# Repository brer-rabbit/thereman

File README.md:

# Annoying Thereman - light sensitive buzzing companion

This repo contains the design and build info for Thereman, a light sensitive buzzing companion.  Very useful for a variety of buzzing sounds.

The Thereman contains two LDRs (Light Dependent Resistors) and a dual 555 timer pretty much like an Atari Punk Console.  The LDRs control pitch and pulse width.

# Build

The kit contains a PCB with the dual 555 timer (a 556), the LDRs, eye LEDs, and some passive components on the front, pre-soldered (lead free).  The back requires soldering a couple components.  I'm assuming you're using regular solder wire (if you're using liquid solder I assume you know what you're doing).

## Prep

Tin the pads first.  Shown below, tin the pads marked in green.  The pads in red should not be tinned.

Optionally: if you'd like a loop of wire to hang the Thereman from, tin the yellow pads.  These are not electrically connected.  You can solder a wire to one or between them to create a loop.

Just a touch of solder for tinning please.  And you don't want solder poking up.  Keep it flat and level so components lay flat.

## Switch

The switch has a few small pads; it's easiest to do this first before the other components clutter the space.  The on/off switch sticks out the side of the Thereman.

Once done congrats!  You've soldered the smallest component of the project.  Everything else ought to be easy.

## Piezo Buzzer

The piezo buzzer is the black square that is responsible for the great sound of the Thereman.  It goes in the very middle; it's not polarized and can be installed in either direction.

## Battery Retainers

Install the top battery retainer.  Two of the three pads keep the battery retainer in place and make an electrical connection.  The middle pad is not soldered.  Of the two pads to solder, the pad that is at the top may be easiest to do first.  Then the pad right next to the piezo.

The bottom two battery retainers need to be oriented so one can insert batteries.

Also, keep the battery retainers slightly apart so they do not touch.

## Cleaning

A bit of isopropyl alcohol can be used for cleaning.  Try not to get alcohol in the switch or the piezo buzzer.

## Flip the switch!

With batteries installed (positive side facing up in retainer) flip the switch.  Your Thereman should now start annoying!

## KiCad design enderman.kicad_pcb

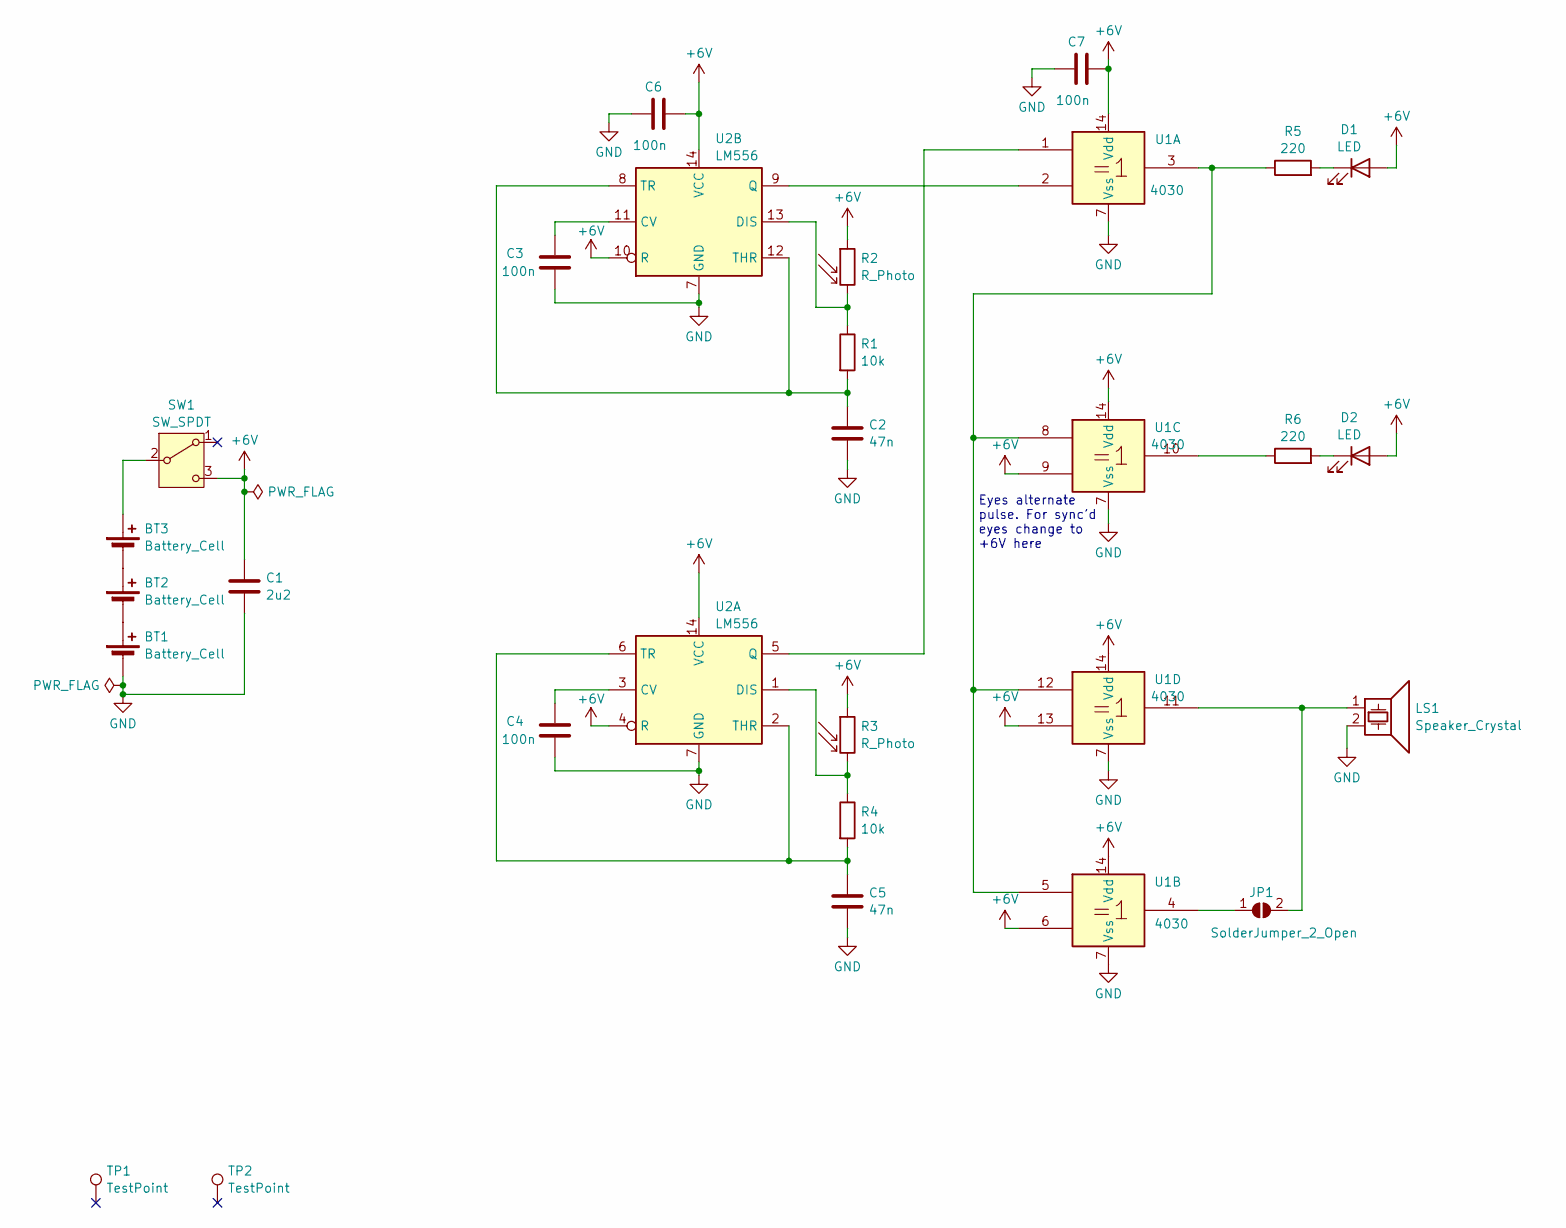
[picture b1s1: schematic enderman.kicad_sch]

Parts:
BT1, BT2, BT3: Battery_Cell; BatteryHolder_Keystone_2996; Digikey 36-2996-ND
C1: 2u2; C_0603_1608Metric
C2, C5: 47n; C_0603_1608Metric; LCSC C1622
C3, C4, C6, C7: 100n; C_0603_1608Metric; LCSC C14663
D1, D2: LED; LED_0805_2012Metric; Digikey 1497-XZFRS54FVF-1CT-ND
JP1: SolderJumper_2_Open; SolderJumper-2_P1.3mm_Open_RoundedPad1.0x1.5mm
LS1: Speaker_Crystal; Piezo PKMCS0909E4000-R1; Digikey 490-9647-1-ND
R1, R4: 10k; R_0603_1608Metric; LCSC C25804
R2, R3: R_Photo; SMD2.4x3.6; LCSC C2904881
R5, R6: 220; R_0603_1608Metric; LCSC C22962
SW1: SW_SPDT; SW_SPDT_PCM12; Digikey 732-13665-1-ND
TP1, TP2: TestPoint; TestPoint_Pad_2.0x2.0mm
U1: 4030; SOIC-14_3.9x8.7mm_P1.27mm; Digikey 296-24348-1-ND
U2: LM556; SOIC-14_3.9x8.7mm_P1.27mm; Digikey 296-1338-1-ND

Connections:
+6V: C1.1, C6.2, C7.2, D1.2 (A), D2.2 (A), R2.1, R3.1, SW1.3 (C), U1.6, U1.9, U1.13, U1.14 (Vdd), U2.4 (R), U2.10 (R), U2.14 (VCC)
GND: BT1.2 (-), C1.2, C2.2, C3.2, C4.2, C5.2, C6.1, C7.1, LS1.2, U1.7 (Vss), U2.7 (GND)
unnamed: BT1.1 (+), BT2.2 (-)
unnamed: BT2.1 (+), BT3.2 (-)
unnamed: BT3.1 (+), SW1.2 (B)
unnamed: D1.1 (K), R5.2
unnamed: D2.1 (K), R6.2
unnamed: JP1.1 (A), U1.4
unnamed: JP1.2 (B), LS1.1, U1.11
unnamed: R5.1, U1.3, U1.5, U1.8, U1.12
unnamed: R6.1, U1.10
unnamed: C4.1, U2.3 (CV)
unnamed: R3.2, R4.1, U2.1 (DIS)
unnamed: U1.1, U2.5 (Q)
unnamed: C5.1, R4.2, U2.2 (THR), U2.6 (TR)
unnamed: C3.1, U2.11 (CV)
unnamed: R1.1, R2.2, U2.13 (DIS)
unnamed: U1.2, U2.9 (Q)
unnamed: C2.1, R1.2, U2.8 (TR), U2.12 (THR)

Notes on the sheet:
Eyes alternate pulse. For sync'd eyes change to +6V here

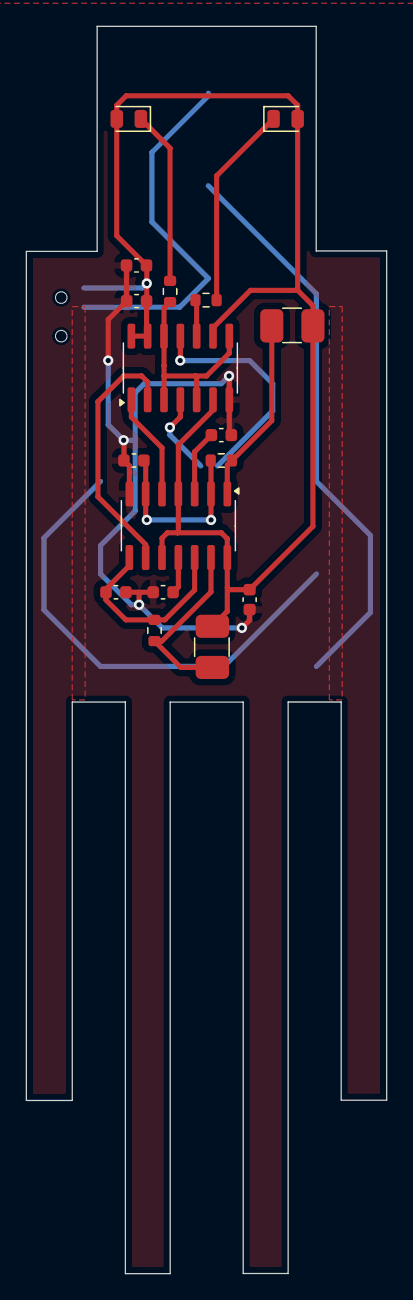
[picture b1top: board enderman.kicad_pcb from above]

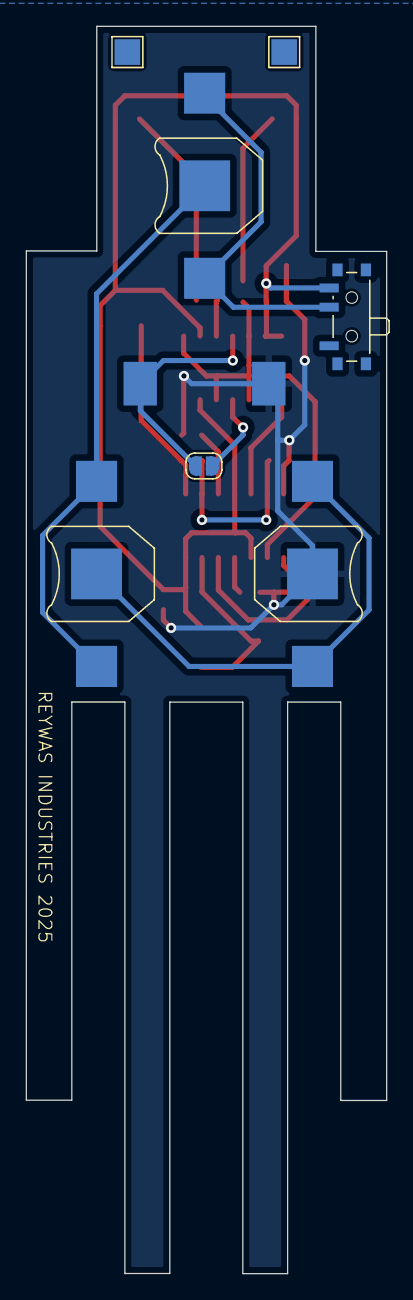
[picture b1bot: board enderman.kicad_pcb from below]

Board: 2 copper layers, 28.0 x 97.0 mm, 25 parts (8 on the bottom side), 19 nets.

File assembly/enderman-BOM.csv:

Comment,Designator,Footprint,LCSC Part #
"2u2","C1","Capacitor_SMD:C_0603_1608Metric","C23630"
"47n","C2,C5","Capacitor_SMD:C_0603_1608Metric","C1622"
"100n","C3,C4,C6","Capacitor_SMD:C_0603_1608Metric","C14663"
"LED","D1,D2","LED_SMD:LED_0805_2012Metric","C7371915"
"10k","R1","Resistor_SMD:R_0603_1608Metric","C25804"
"R_Photo","R2,R3","Library:SMD2.4x3.6","C2904880"
"220","R5,R6","Resistor_SMD:R_0603_1608Metric","C22962"
"LM556","U1","Package_SO:SOIC-14_3.9x8.7mm_P1.27mm","C18164404"

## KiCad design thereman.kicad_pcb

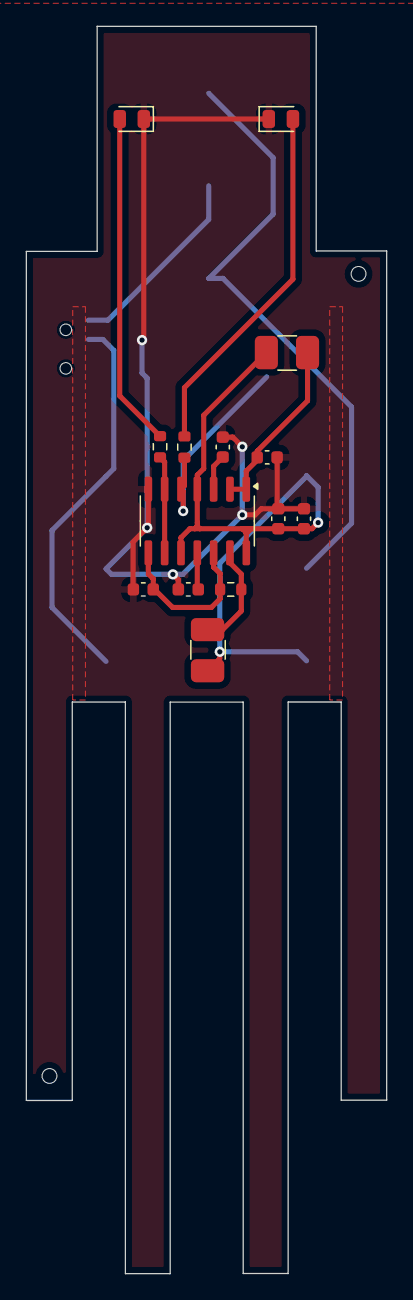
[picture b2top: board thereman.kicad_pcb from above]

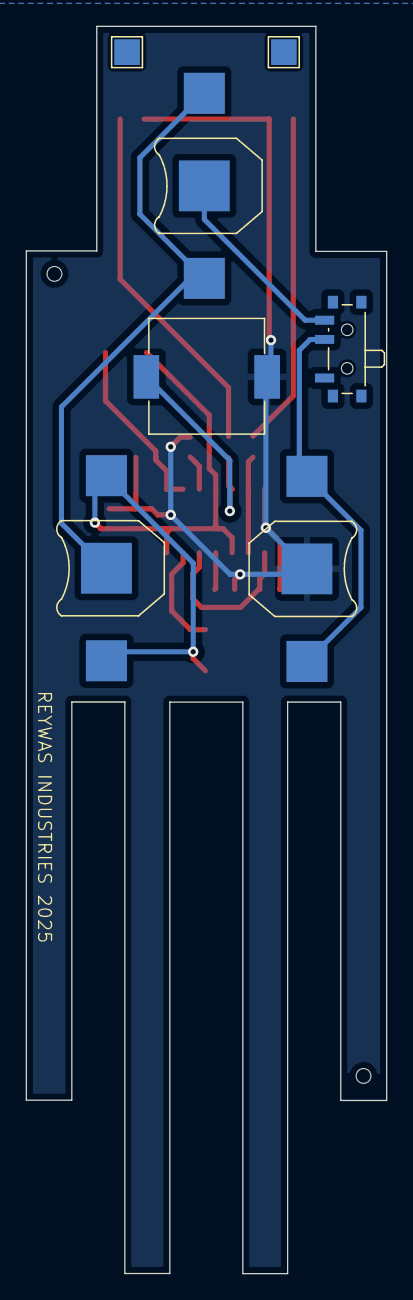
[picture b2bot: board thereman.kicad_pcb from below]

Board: 2 copper layers, 28.0 x 97.0 mm, 21 parts (7 on the bottom side), 14 nets.

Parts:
BT1, BT2, BT3: Battery_Cell; BatteryHolder_Keystone_2996
C1: 1u; C_0603_1608Metric
C2, C5: 47n; C_0603_1608Metric
C3, C4, C6: 100n; C_0603_1608Metric
D1, D2: LED; LED_0805_2012Metric
LS1: Speaker_Crystal; Piezo PKMCS0909E4000-R1
R1: 10k; R_0603_1608Metric
R2, R3: R_Photo; SMD2.4x3.6
R5, R6: 220; R_0603_1608Metric
SW1: SW_SPDT; SW_SPDT_PCM12
TP1, TP2: TestPoint; TestPoint_Pad_2.0x2.0mm
U1: LM556; SOIC-14_3.9x8.7mm_P1.27mm

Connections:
+6V: BT2.1 (+), C1.1, C6.2, R2.1, R3.1, U1.4 (R), U1.10 (R), U1.14 (VCC)
GND: BT1.2 (-), C1.2, C2.2, C3.2, C4.2, C5.2, C6.1, D1.1 (K), D2.1 (K), LS1.2, U1.7 (GND)
unnamed: BT1.1 (+), SW1.2 (B)
unnamed: BT2.2 (-), BT3.1 (+)
unnamed: BT3.2 (-), SW1.3 (C)
unnamed: D1.2 (A), R5.2
unnamed: D2.2 (A), R6.2
unnamed: C4.1, U1.3 (CV)
unnamed: C5.1, R3.2, U1.1 (DIS), U1.2 (THR)
unnamed: LS1.1, R6.1, U1.5 (Q)
unnamed: R5.1, U1.6 (TR), U1.9 (Q)
unnamed: C3.1, U1.11 (CV)
unnamed: R1.1, R2.2, U1.13 (DIS)
unnamed: C2.1, R1.2, U1.8 (TR), U1.12 (THR)

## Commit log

2025-02-24 v2.0 RTM
2025-03-05 minimize vias
2025-03-05 routed atari punk console version
2025-03-07 updated piezo footprint. Better routing. Added on/off switch. Hid some vias under chip.
2025-03-07 add library path
2025-03-19 atari punk version
2025-03-20 fix typo
2025-03-20 add option for 2x drive to buzzer
2025-03-20 xor routing
2025-03-20 routed xor version with better placement of switch
2025-03-22 file renames
2025-03-22 rename
2025-03-23 add build images and readme
2025-03-23 fix typos
2025-03-24 annotate build pics
2025-03-25 additional instructions for build
2025-03-26 add a few more photos
